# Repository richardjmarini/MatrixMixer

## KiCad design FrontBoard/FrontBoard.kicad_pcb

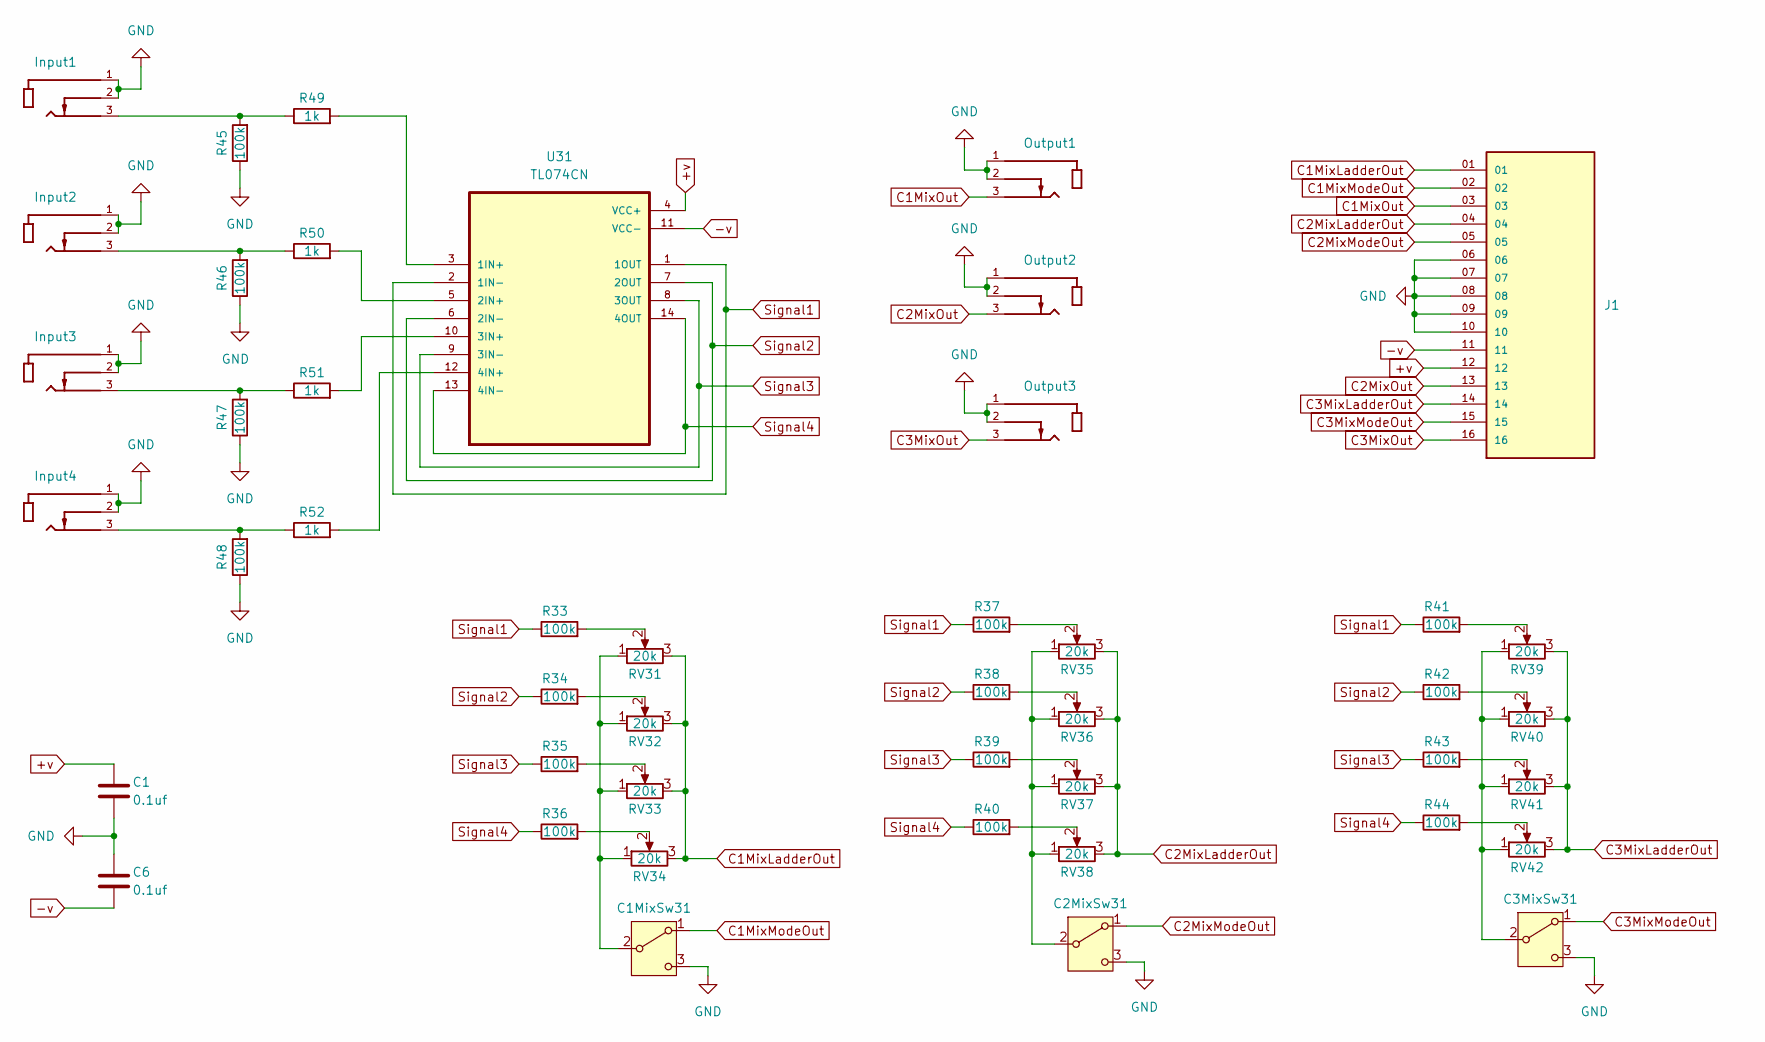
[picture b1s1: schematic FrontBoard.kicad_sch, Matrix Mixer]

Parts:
C1, C6: 0.1uf; C_Disc_D7.5mm_W4.4mm_P5.00mm
C1MixSw31, C2MixSw31, C3MixSw31: SW_SPDT; SW_100SP1T6B11M1REH
Input1, Input2, Input3, Input4: PJ398SM-12; THONK_PJ398SM-12; PARTREV 1
J1: ESQ-116-33-L-S; SAMTEC_ESQ-116-33-L-S; PARTREV R
Output1, Output2, Output3: PJ398SM-12; THONK_PJ398SM-12; PARTREV 1
R33, R34, R35, R36, R37, R38, R39, R40, R41, R42, R43, R44, R45, R46, R47, R48: 100k; R_Axial_DIN0207_L6.3mm_D2.5mm_P10.16mm_Horizontal
R49, R50, R51, R52: 1k; R_Axial_DIN0207_L6.3mm_D2.5mm_P10.16mm_Horizontal
RV31, RV32, RV33, RV34, RV35, RV36, RV37, RV38, RV39, RV40, RV41, RV42: 20k; Potentiometer_TT_P0915N
U31: TL074CN; DIP794W45P254L1969H508Q14

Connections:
+v: C1.1, J1.12, U31.4 (VCC+)
-v: C6.1, J1.11, U31.11 (VCC-)
C1MixLadderOut: J1.01, RV31.3, RV32.3, RV33.3, RV34.3
C1MixModeOut: C1MixSw31.1 (A), J1.02
C1MixOut: J1.03, Output1.3
C2MixLadderOut: J1.04, RV35.3, RV36.3, RV37.3, RV38.3
C2MixModeOut: C2MixSw31.1 (A), J1.05
C2MixOut: J1.13, Output2.3
C3MixLadderOut: J1.14, RV39.3, RV40.3, RV41.3, RV42.3
C3MixModeOut: C3MixSw31.1 (A), J1.15
C3MixOut: J1.16, Output3.3
GND: C1.2, C1MixSw31.3 (C), C2MixSw31.3 (C), C3MixSw31.3 (C), C6.2, Input1.1, Input1.2, Input2.1, Input2.2, Input3.1, Input3.2, Input4.1, Input4.2, J1.06, J1.07, J1.08, J1.09, J1.10, Output1.1, Output1.2, Output2.1, Output2.2, Output3.1, Output3.2, R45.1, R46.1, R47.1, R48.1
unnamed: C1MixSw31.2 (B), RV31.1, RV32.1, RV33.1, RV34.1
unnamed: C2MixSw31.2 (B), RV35.1, RV36.1, RV37.1, RV38.1
unnamed: C3MixSw31.2 (B), RV39.1, RV40.1, RV41.1, RV42.1
unnamed: Input1.3, R45.2, R49.1
unnamed: Input2.3, R46.2, R50.1
unnamed: Input3.3, R47.2, R51.1
unnamed: Input4.3, R48.2, R52.1
unnamed: R33.2, RV31.2
unnamed: R34.2, RV32.2
unnamed: R35.2, RV33.2
unnamed: R36.2, RV34.2
unnamed: R37.2, RV35.2
unnamed: R38.2, RV36.2
unnamed: R39.2, RV37.2
unnamed: R40.2, RV38.2
unnamed: R41.2, RV39.2
unnamed: R42.2, RV40.2
unnamed: R43.2, RV41.2
unnamed: R44.2, RV42.2
unnamed: R49.2, U31.3 (1IN+)
unnamed: R50.2, U31.5 (2IN+)
unnamed: R51.2, U31.10 (3IN+)
unnamed: R52.2, U31.12 (4IN+)
Signal1: R33.1, R37.1, R41.1, U31.1 (1OUT), U31.2 (1IN-)
Signal2: R34.1, R38.1, R42.1, U31.6 (2IN-), U31.7 (2OUT)
Signal3: R35.1, R39.1, R43.1, U31.8 (3OUT), U31.9 (3IN-)
Signal4: R36.1, R40.1, R44.1, U31.13 (4IN-), U31.14 (4OUT)

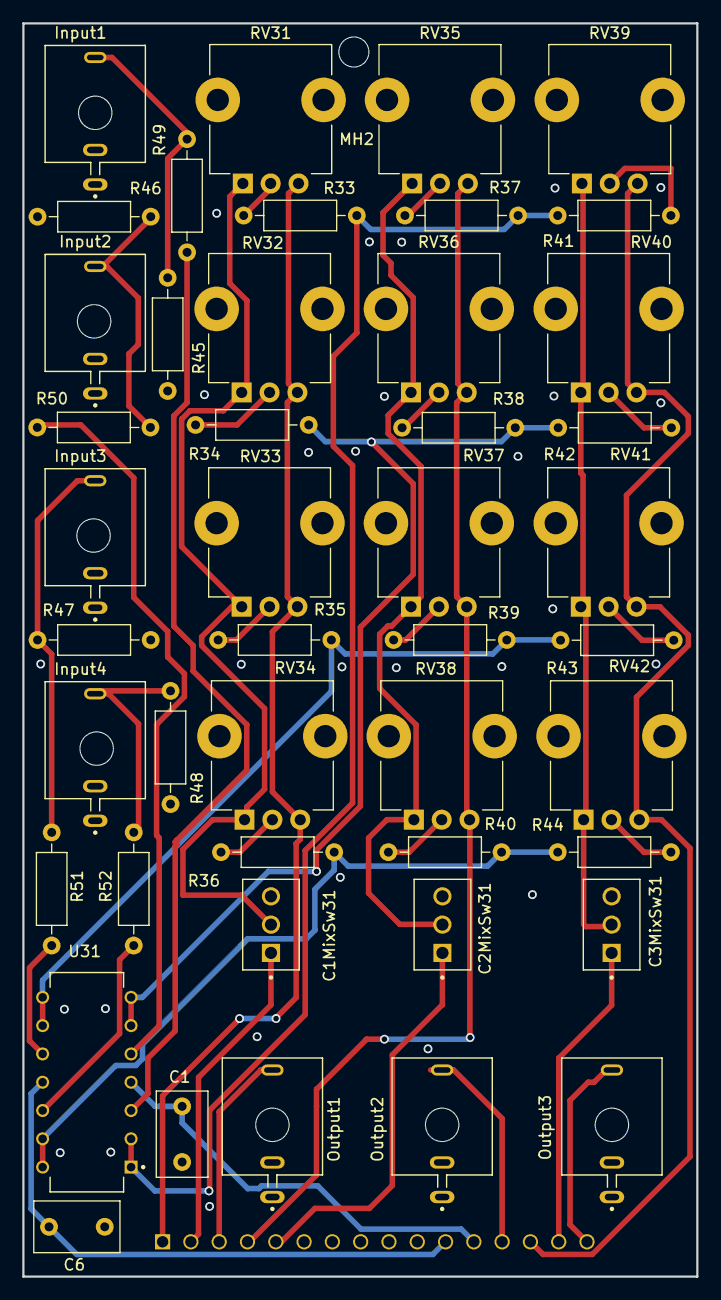
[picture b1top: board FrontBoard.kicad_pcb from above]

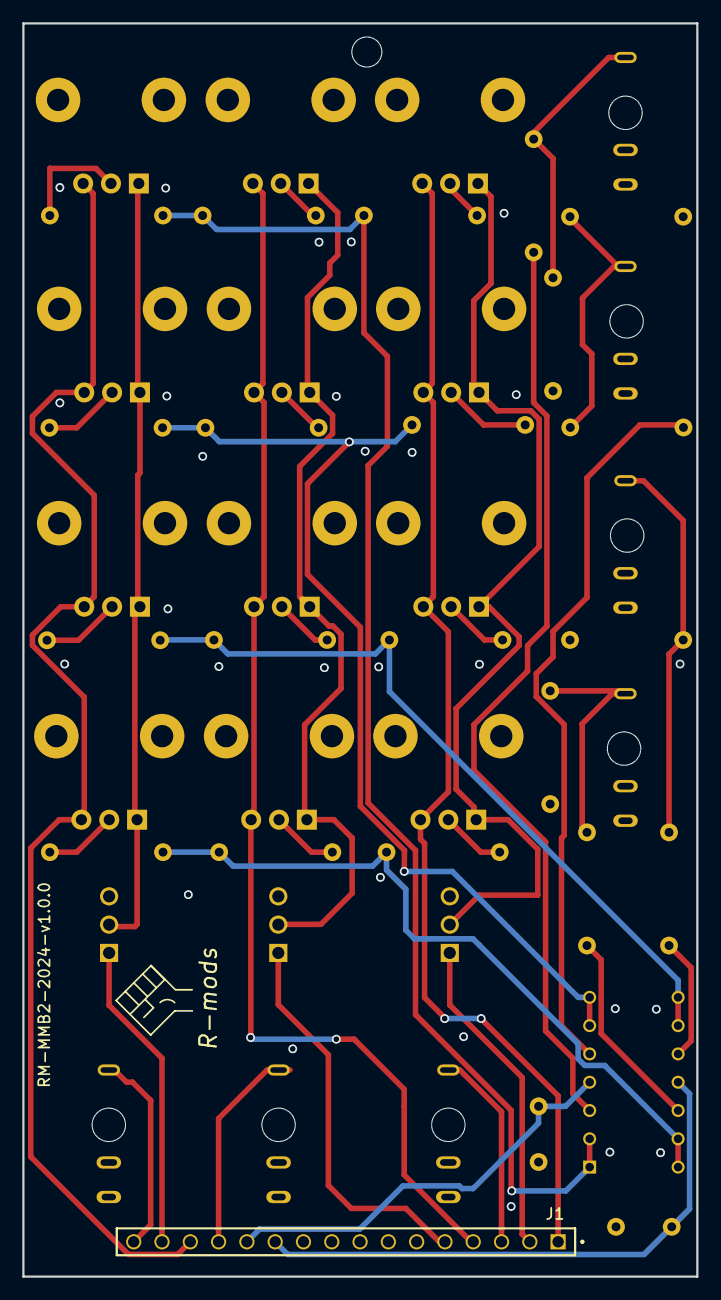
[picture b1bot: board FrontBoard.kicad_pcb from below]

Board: 4 copper layers, 60.5 x 112.5 mm, 54 parts (6 on the bottom side), 39 nets.

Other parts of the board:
Input2_PCBH, Input3_PCBH, Input4_PCBH: MountingHole_3mm
Input_PCBH: MountingHole_3mm
MH2: MountingHole_2.7mm_M2.5
Output1_PCBH, Output2_PCBH, Output3_PCBH: MountingHole_3mm

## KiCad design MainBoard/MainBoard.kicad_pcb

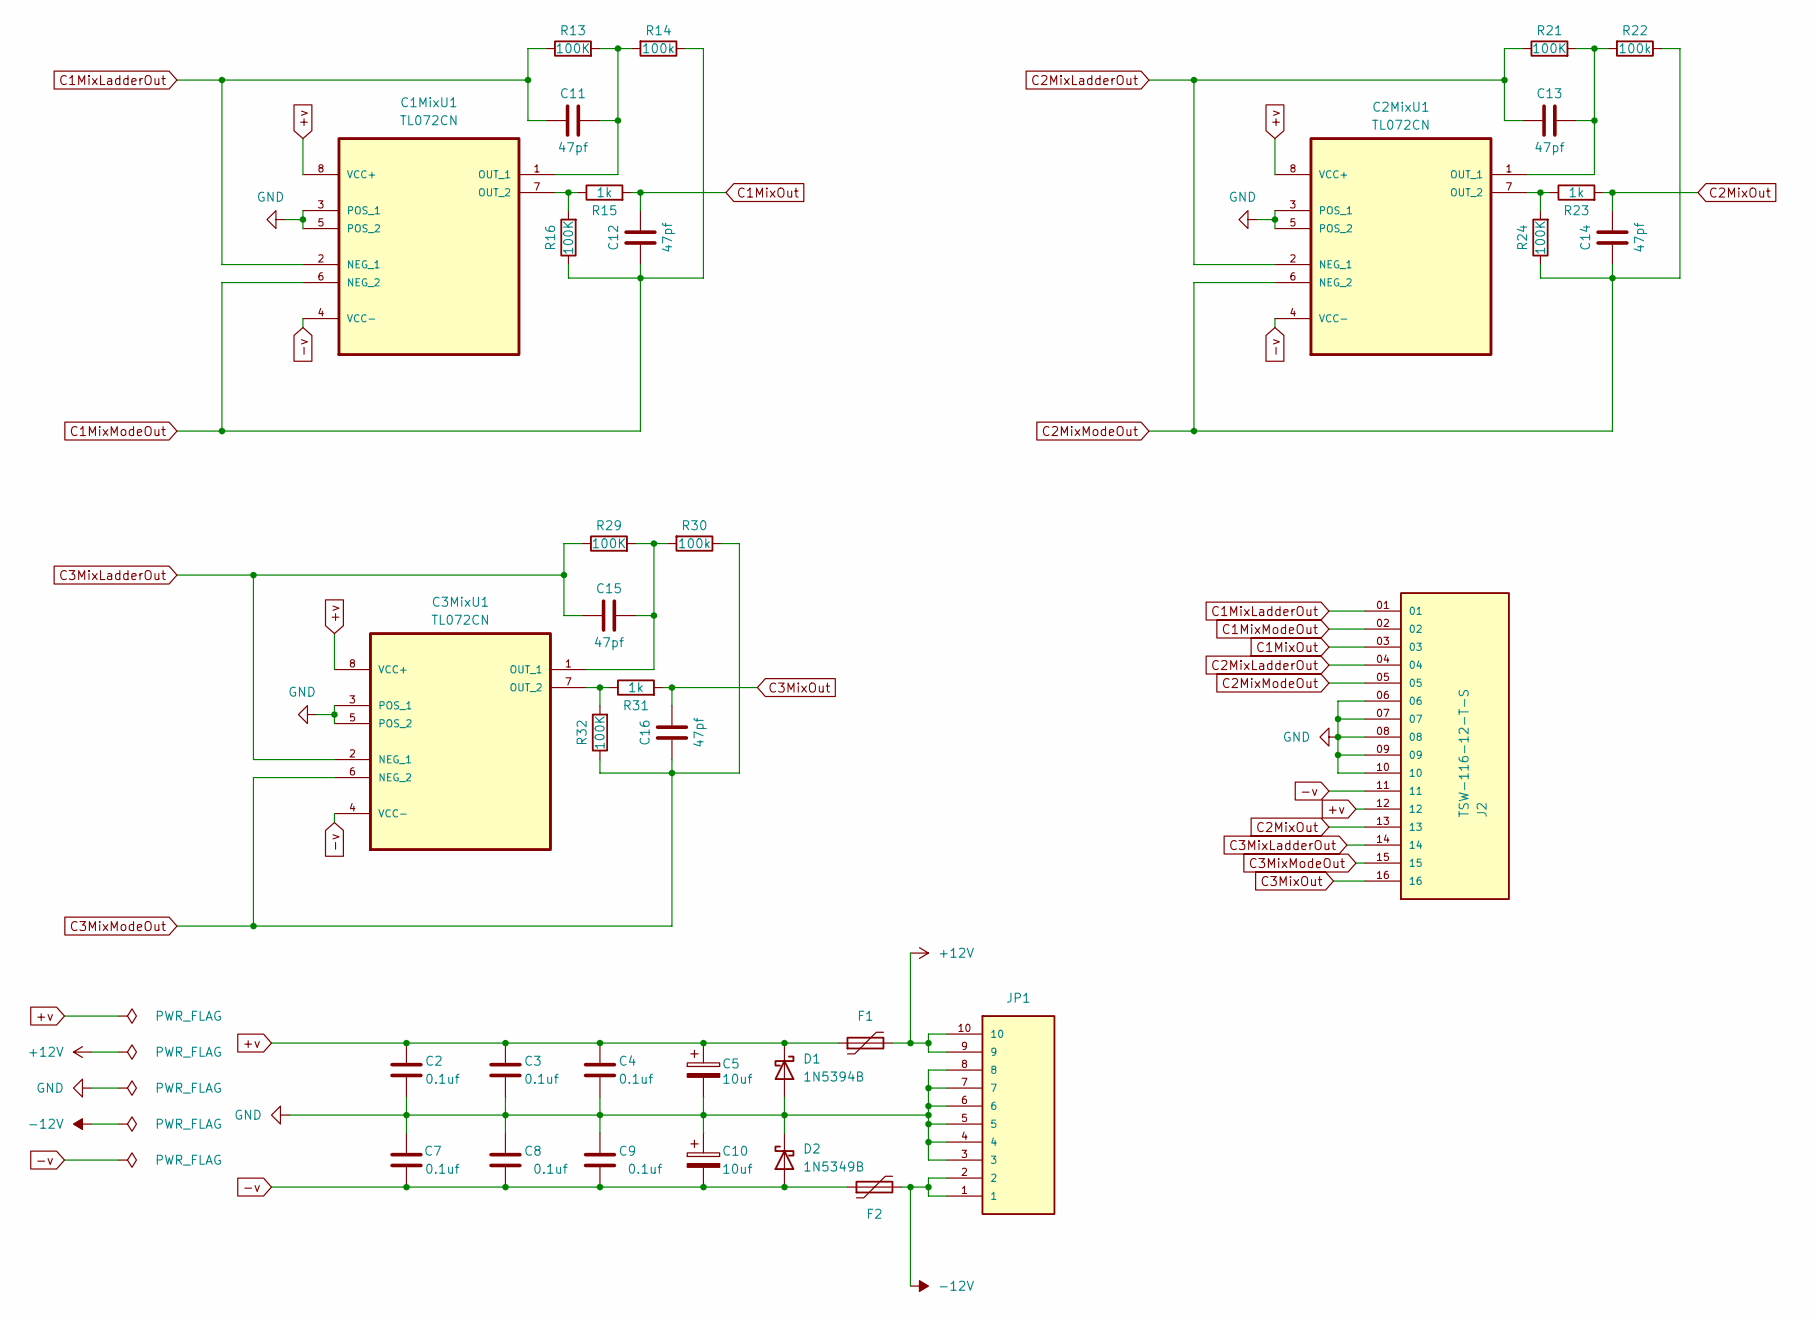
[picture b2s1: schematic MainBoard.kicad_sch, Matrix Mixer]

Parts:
C1MixU1, C2MixU1, C3MixU1: TL072CN; DIP254P762X533-8; MPN TL072CN
C2, C3, C4, C7, C8, C9: 0.1uf; C_Disc_D7.5mm_W4.4mm_P5.00mm
C5, C10: 10uf; CP_Radial_D5.0mm_P2.50mm
C11, C12, C13, C14, C15, C16: 47pf; C_Disc_D7.5mm_W4.4mm_P5.00mm
D1: 1N5394B; P2_DO-201
D2: 1N5349B; P2_DO-201
F1, F2: type="R" model="Polyfuse" lib=""; FUSRB510W81L1358T310H1980
J2: TSW-116-12-T-S; SAMTEC_TSW-116-12-T-S; PARTREV R
JP1: 1761681-3; TE_1761681-3
R13, R16, R21, R24, R29, R32: 100K; R_Axial_DIN0207_L6.3mm_D2.5mm_P10.16mm_Horizontal
R14, R22, R30: 100k; R_Axial_DIN0207_L6.3mm_D2.5mm_P10.16mm_Horizontal
R15, R23, R31: 1k; R_Axial_DIN0207_L6.3mm_D2.5mm_P10.16mm_Horizontal

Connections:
+12V: F1.2, JP1.9, JP1.10
+v: C1MixU1.8 (VCC+), C2.1, C2MixU1.8 (VCC+), C3.1, C3MixU1.8 (VCC+), C4.1, C5.1, D1.1 (K), F1.1, J2.12
-12V: F2.2, JP1.1, JP1.2
-v: C1MixU1.4 (VCC-), C2MixU1.4 (VCC-), C3MixU1.4 (VCC-), C7.1, C8.1, C9.1, C10.2, D2.2 (A), F2.1, J2.11
C1MixLadderOut: C1MixU1.2 (NEG_1), C11.2, J2.01, R13.1
C1MixModeOut: C1MixU1.6 (NEG_2), C12.2, J2.02, R14.1, R16.1
C1MixOut: C12.1, J2.03, R15.2
C2MixLadderOut: C2MixU1.2 (NEG_1), C13.2, J2.04, R21.1
C2MixModeOut: C2MixU1.6 (NEG_2), C14.2, J2.05, R22.1, R24.1
C2MixOut: C14.1, J2.13, R23.2
C3MixLadderOut: C3MixU1.2 (NEG_1), C15.2, J2.14, R29.1
C3MixModeOut: C3MixU1.6 (NEG_2), C16.2, J2.15, R30.1, R32.1
C3MixOut: C16.1, J2.16, R31.2
GND: C1MixU1.3 (POS_1), C1MixU1.5 (POS_2), C2.2, C2MixU1.3 (POS_1), C2MixU1.5 (POS_2), C3.2, C3MixU1.3 (POS_1), C3MixU1.5 (POS_2), C4.2, C5.2, C7.2, C8.2, C9.2, C10.1, D1.2 (A), D2.1 (K), J2.06, J2.07, J2.08, J2.09, J2.10, JP1.3, JP1.4, JP1.5, JP1.6, JP1.7, JP1.8
unnamed: C1MixU1.1 (OUT_1), C11.1, R13.2, R14.2
unnamed: C1MixU1.7 (OUT_2), R15.1, R16.2
unnamed: C2MixU1.1 (OUT_1), C13.1, R21.2, R22.2
unnamed: C2MixU1.7 (OUT_2), R23.1, R24.2
unnamed: C3MixU1.1 (OUT_1), C15.1, R29.2, R30.2
unnamed: C3MixU1.7 (OUT_2), R31.1, R32.2

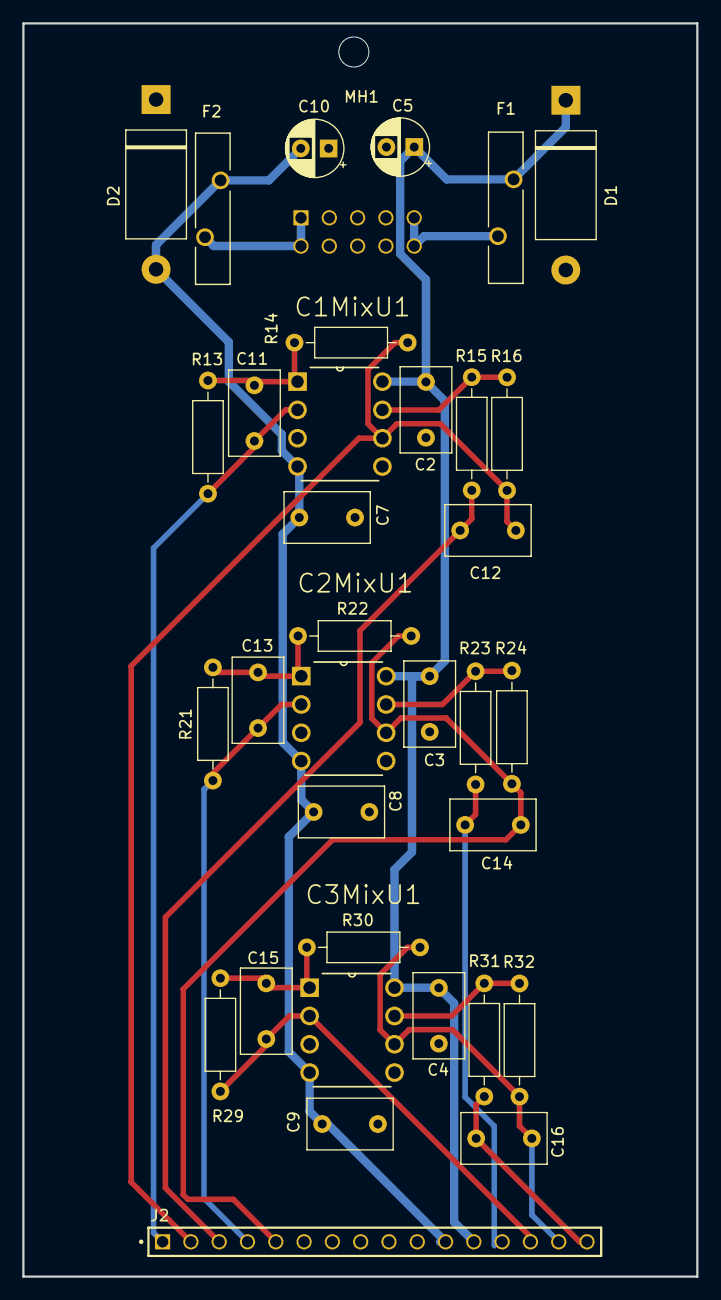
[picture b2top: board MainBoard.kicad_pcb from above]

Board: 4 copper layers, 60.5 x 112.5 mm, 36 parts (1 on the bottom side), 20 nets.

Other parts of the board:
MH1: MountingHole_2.7mm_M2.5

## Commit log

2024-04-06 corrected duplicate annotations, simplified signal path, passes all DRC checks
2024-04-06 assigned some footprints
2024-06-17 laid out MainBoard, added 3d models
2024-07-15 added footprints and 3dmodels
2024-07-29 updated 200 ohm resister on output to 1k for more reverse protection
2024-08-02 faceplate aligned with potiemeters, jacks and switches
2024-08-04 replaced SPST swtiches with sub-toggle, alinged switch faceplace holes, updated 3d models
2024-08-05 added additional vias on layer transitions
2024-08-05 sent to produciton
